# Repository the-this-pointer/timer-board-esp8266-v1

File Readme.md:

Tiny timer board supporting wifi with just one output channel.
This repository contains all neccessary files of the project.

THE SOFTWARE IS PROVIDED "AS IS", WITHOUT WARRANTY OF ANY KIND

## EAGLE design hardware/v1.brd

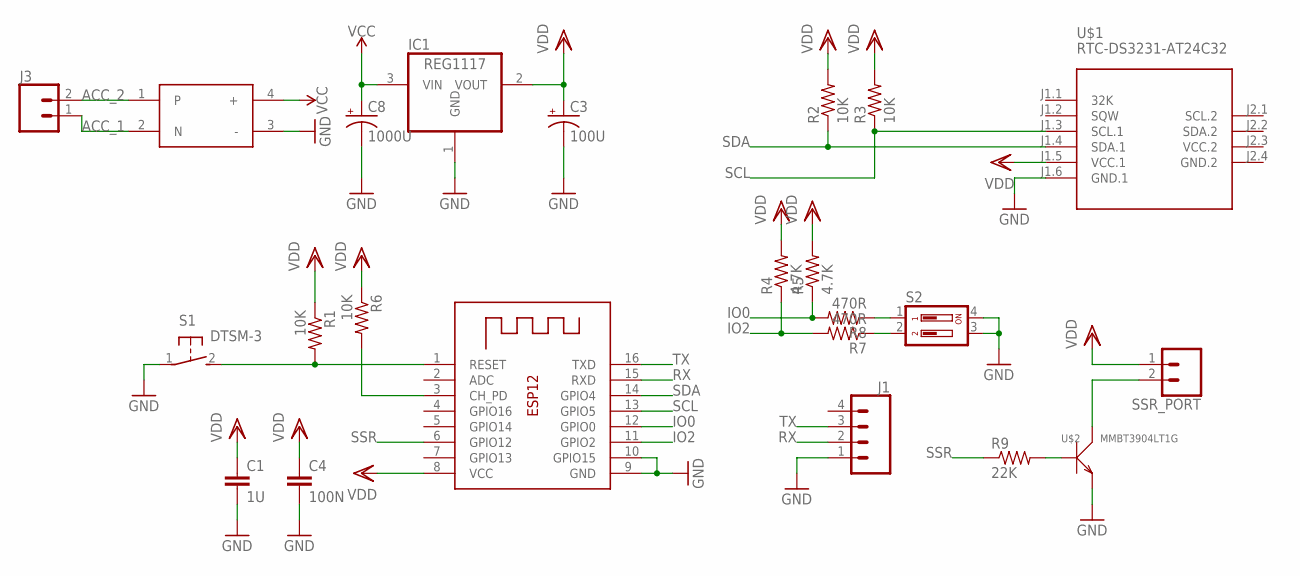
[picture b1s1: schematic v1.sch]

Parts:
C1: 1U; 1206
C3: 100U; CPOL-RADIAL-100UF-25V
C4: 100N; 1206
C8: 1000U; CPOL-RADIAL-5MM-10MM
IC1: REG1117; SOT223
J1: CONN_04; 1X04
J3: CONN_023.5MM; SCREWTERMINAL-3.5MM-2
R1, R2, R3, R6: 10K; 1206
R4, R5: 4.7K; 1206
R7, R8: 470R; 1206
R9: 22K; 1206
S1: DTSM-3
S2: DP02; DP-02
SSR_PORT: CONN_023.5MM; SCREWTERMINAL-3.5MM-2
U$1: RTC-DS3231-AT24C32
U$2: MMBT3904LT1G; SOT-23
U$3: AC_DC
X1: ESP-12

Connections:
ACC_1: J3.1, U$3.2 (N)
ACC_2: J3.2, U$3.1
GND: C1.2, C3.2 (-), C4.2, C8.-, IC1.1 (GND), J1.1, S1.1, S2.3, S2.4, U$1.J1.6 (GND.1), U$2.2 (E), U$3.3 (-), X1.9 (GND), X1.10 (GPIO15)
GND.2: U$1.J2.4 (GND.2)
IO0: R5.1, R8.2, X1.12 (GPIO0)
IO2: R4.1, R7.2, X1.11 (GPIO2)
unnamed: R1.2, S1.2, X1.1 (RESET)
unnamed: R6.2, X1.3 (CH_PD)
unnamed: R7.1, S2.2
unnamed: R8.1, S2.1
unnamed: R9.2, U$2.1 (B)
unnamed: SSR_PORT.2, U$2.3 (C)
RX: J1.2, X1.15 (RXD)
SCL: R3.1, U$1.J1.3 (SCL.1), X1.13 (GPIO5)
SDA: R2.1, U$1.J1.4 (SDA.1), X1.14 (GPIO4)
SSR: R9.1, X1.6 (GPIO12)
TX: J1.3, X1.16 (TXD)
VCC: C8.+, IC1.3 (VIN), U$3.4 (+)
VCC.2: U$1.J2.3 (VCC.2)
VDD: C1.1, C3.1 (+), C4.1, IC1.2 (VOUT), R1.1, R2.2, R3.2, R4.2, R5.2, R6.1, SSR_PORT.1, U$1.J1.5 (VCC.1), X1.8 (VCC)

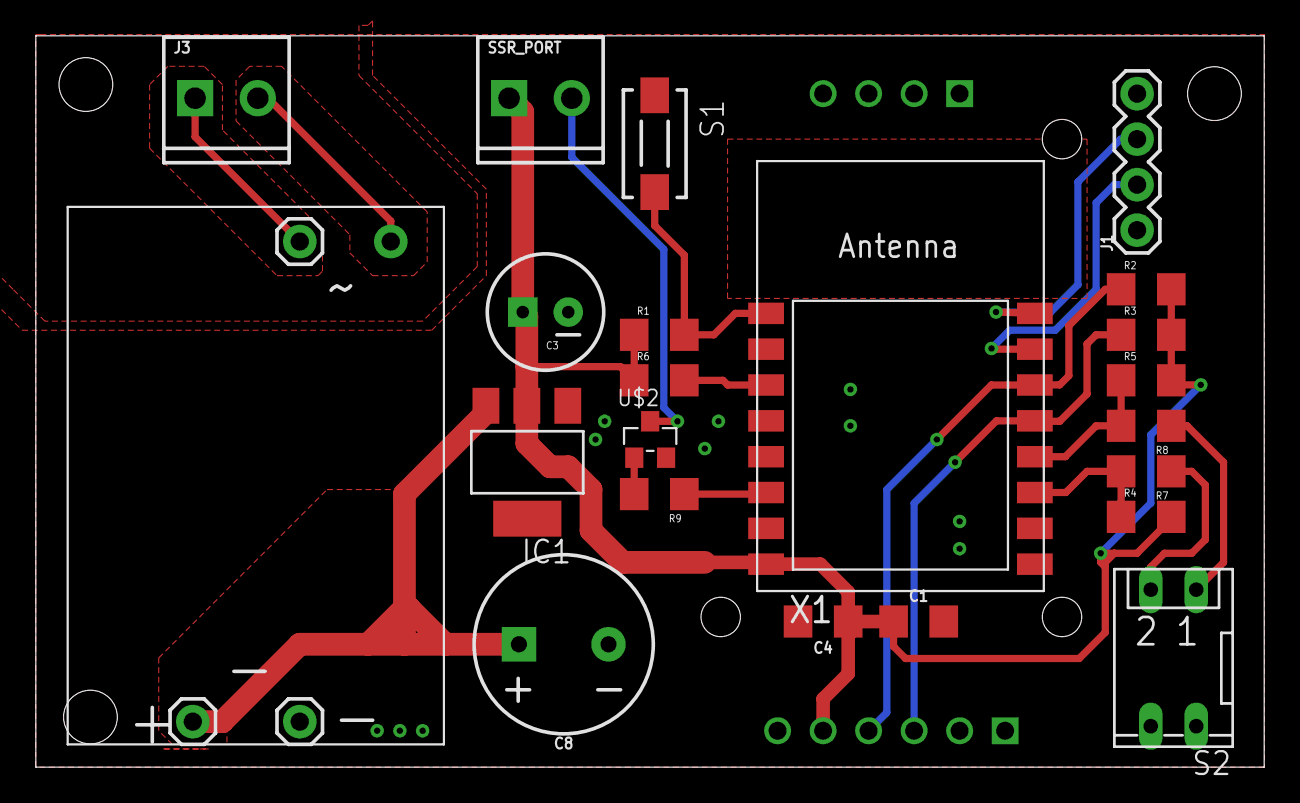
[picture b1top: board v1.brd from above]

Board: 2 copper layers, 68.6 x 40.8 mm, 23 parts (1 on the bottom side), 18 nets.

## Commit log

2025-04-17 fw: version 2 with new features and new ui
2025-04-17 fw: weekday bug with rtc module

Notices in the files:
parts and their libraries:
SparkFun-Capacitors: Licensing: Creative Commons ShareAlike 4.0 International - https://creativecommons.org/licenses/by-sa/4.0
SparkFun-Passives: Licensing: CC v3.0 Share-Alike You are welcome to use this library for commercial purposes.
